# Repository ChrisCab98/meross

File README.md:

# meross
Meross SmartSurge compatible with HomeKit

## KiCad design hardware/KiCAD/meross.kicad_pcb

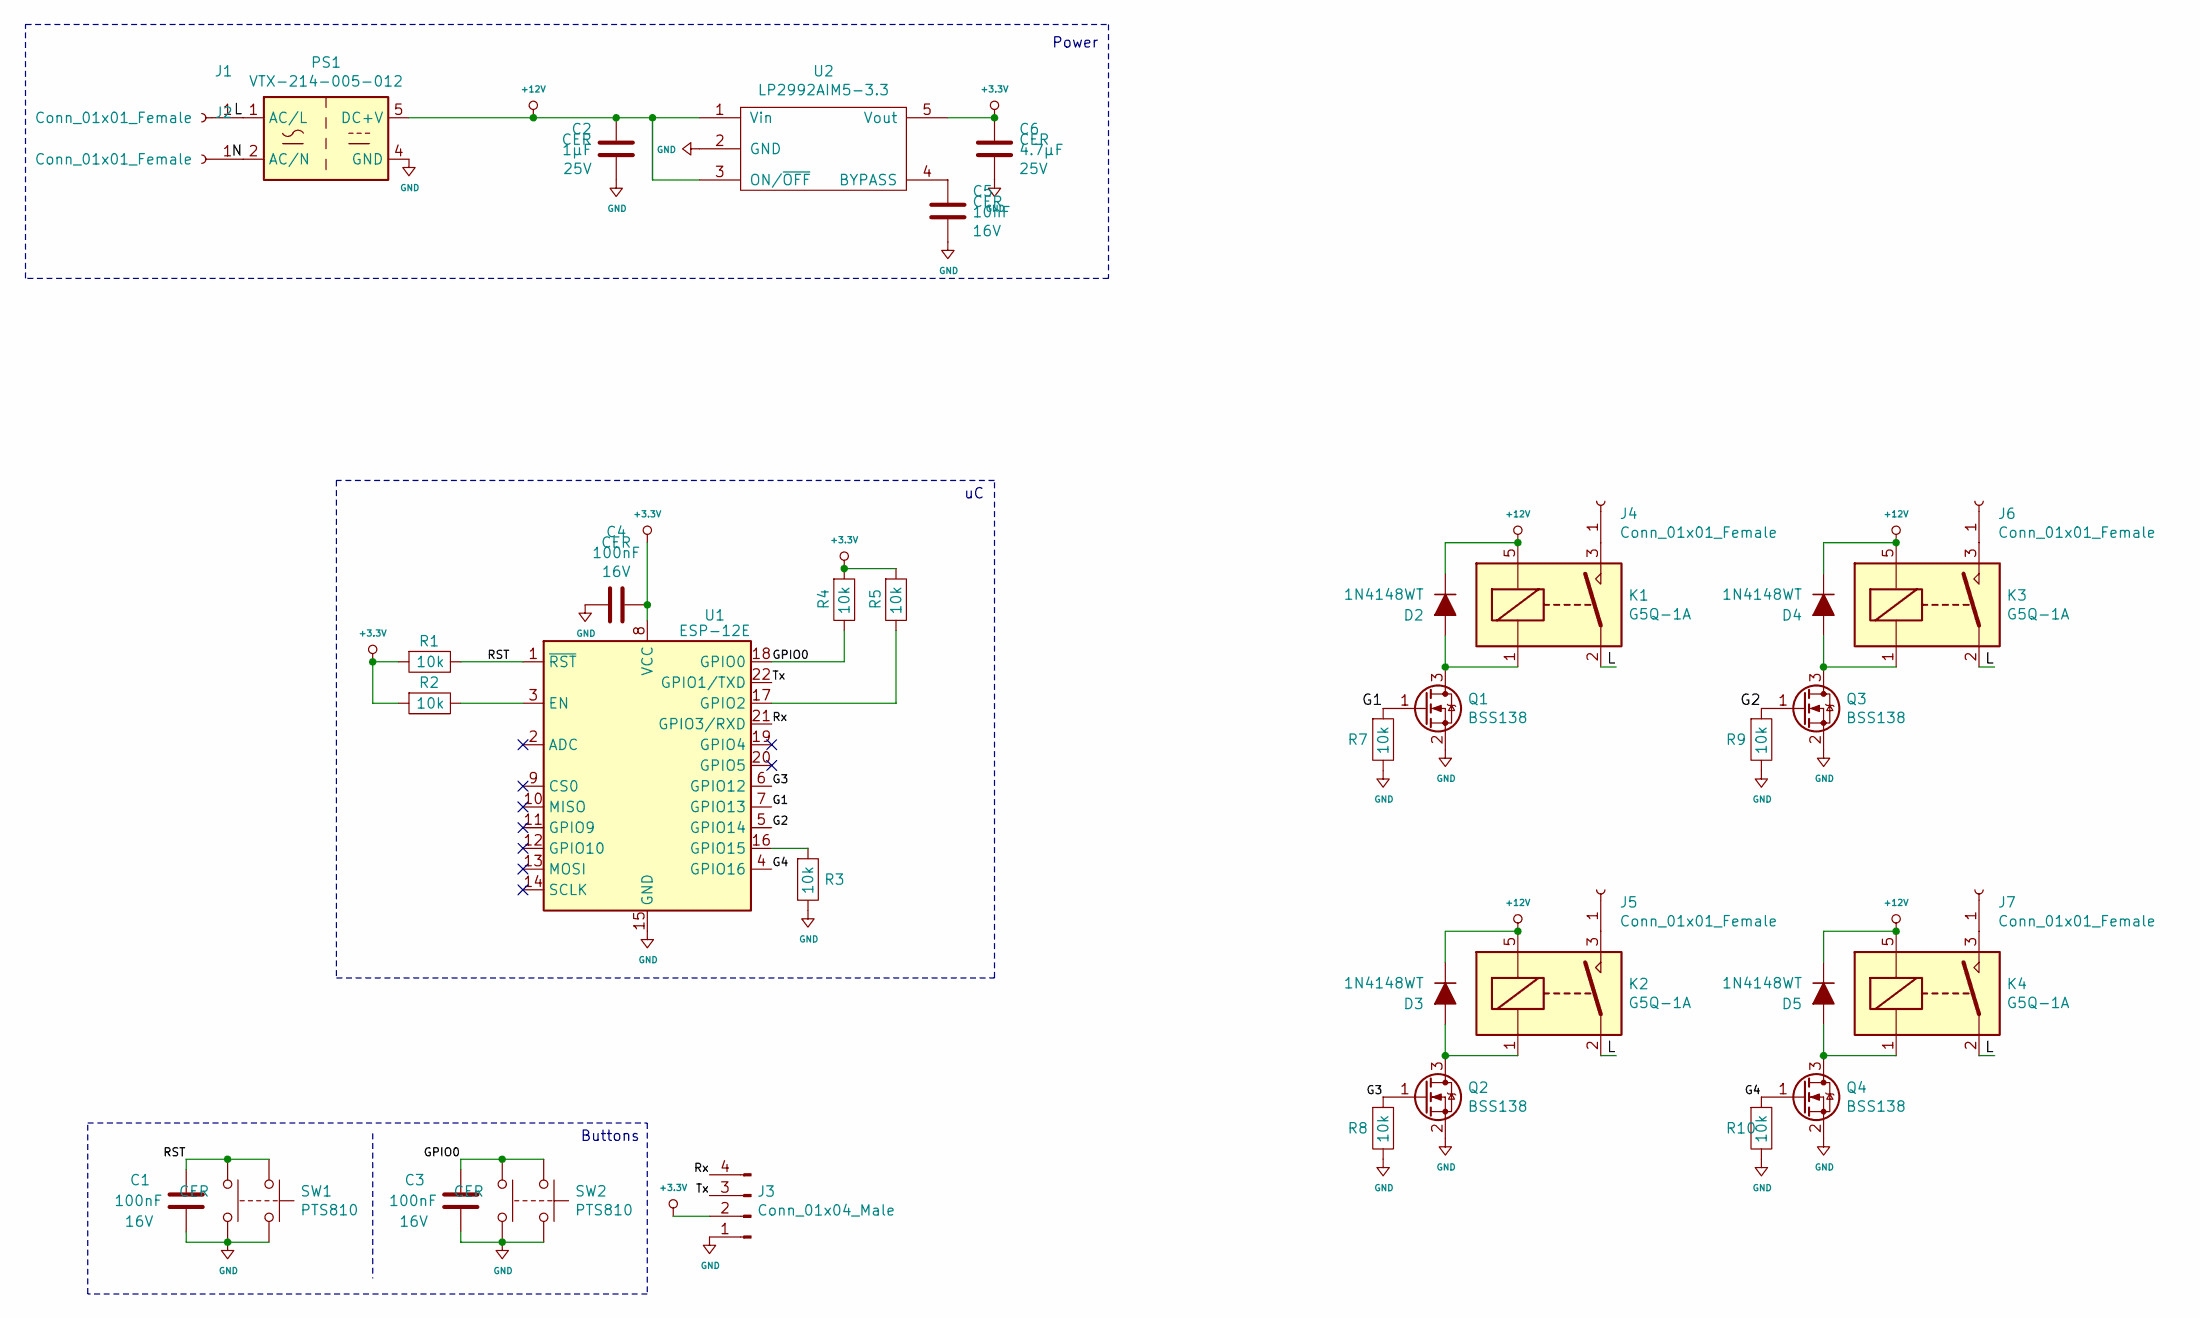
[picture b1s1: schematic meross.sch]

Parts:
C1, C3, C4: C_0029; C_0603
C2: C_0037; C_0603
C5: C_0017; C_0603
C6: C_0036; C_0603
D2, D3, D4, D5: D_0022; D_SOD-523
J1, J2, J4, J5, J6, J7: Conn_01x01_Female; TestPoint_Loop_D2.54mm_Drill1.5mm_Beaded
J3: Conn_01x04_Male; PinHeader_2x02_P2.54mm_Vertical
K1, K2, K3, K4: G5Q-1A; Relay_SPST_Omron-G5Q-1A
PS1: VTX-214-005-012
Q1, Q2, Q3, Q4: BSS138; SOT-23
R1, R2, R3, R4, R5, R7, R8, R9, R10: R_0065; R_0603
SW1, SW2: SW_0003; PTS810
U1: ESP-12E
U2: U_0005; SOT_23-5

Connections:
+3.3V: C4.1, C6.1, J3.2, R1.1, R2.1, R4.1, R5.1, U1.8 (VCC), U2.5 (Vout)
+12V: C2.2, D2.1 (K), D3.1 (K), D4.1 (K), D5.1 (K), K1.5, K2.5, K3.5, K4.5, PS1.5 (DC+V), U2.1 (Vin), U2.3 (ON/~OFF)
/G1: Q1.1 (G), R7.1, U1.7 (GPIO13)
/G2: Q3.1 (G), R9.1, U1.5 (GPIO14)
/G3: Q2.1 (G), R8.1, U1.6 (GPIO12)
/G4: Q4.1 (G), R10.1, U1.4 (GPIO16)
/GPIO0: C3.2, R4.2, SW2.1, SW2.2, U1.18 (GPIO0)
/L: J1.1, K1.2, K2.2, K3.2, K4.2, PS1.1 (AC/L)
/N: J2.1, PS1.2 (AC/N)
/RST: C1.2, R1.2, SW1.1, SW1.2, U1.1 (~RST)
/Rx: J3.4, U1.21 (GPIO3/RXD)
/Tx: J3.3, U1.22 (GPIO1/TXD)
GND: C1.1, C2.1, C3.1, C4.2, C5.2, C6.2, J3.1, PS1.4 (GND), Q1.2 (S), Q2.2 (S), Q3.2 (S), Q4.2 (S), R3.2, R7.2, R8.2, R9.2, R10.2, SW1.3, SW1.4, SW2.3, SW2.4, U1.15 (GND), U2.2 (GND)
unnamed: C5.1, U2.4 (BYPASS)
unnamed: D2.2 (A), K1.1, Q1.3 (D)
unnamed: D3.2 (A), K2.1, Q2.3 (D)
unnamed: D4.2 (A), K3.1, Q3.3 (D)
unnamed: D5.2 (A), K4.1, Q4.3 (D)
unnamed: J4.1, K1.3
unnamed: J5.1, K2.3
unnamed: J6.1, K3.3
unnamed: J7.1, K4.3
unnamed: R2.2, U1.3 (EN)
unnamed: R3.1, U1.16 (GPIO15)
unnamed: R5.2, U1.17 (GPIO2)

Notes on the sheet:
Buttons
Power

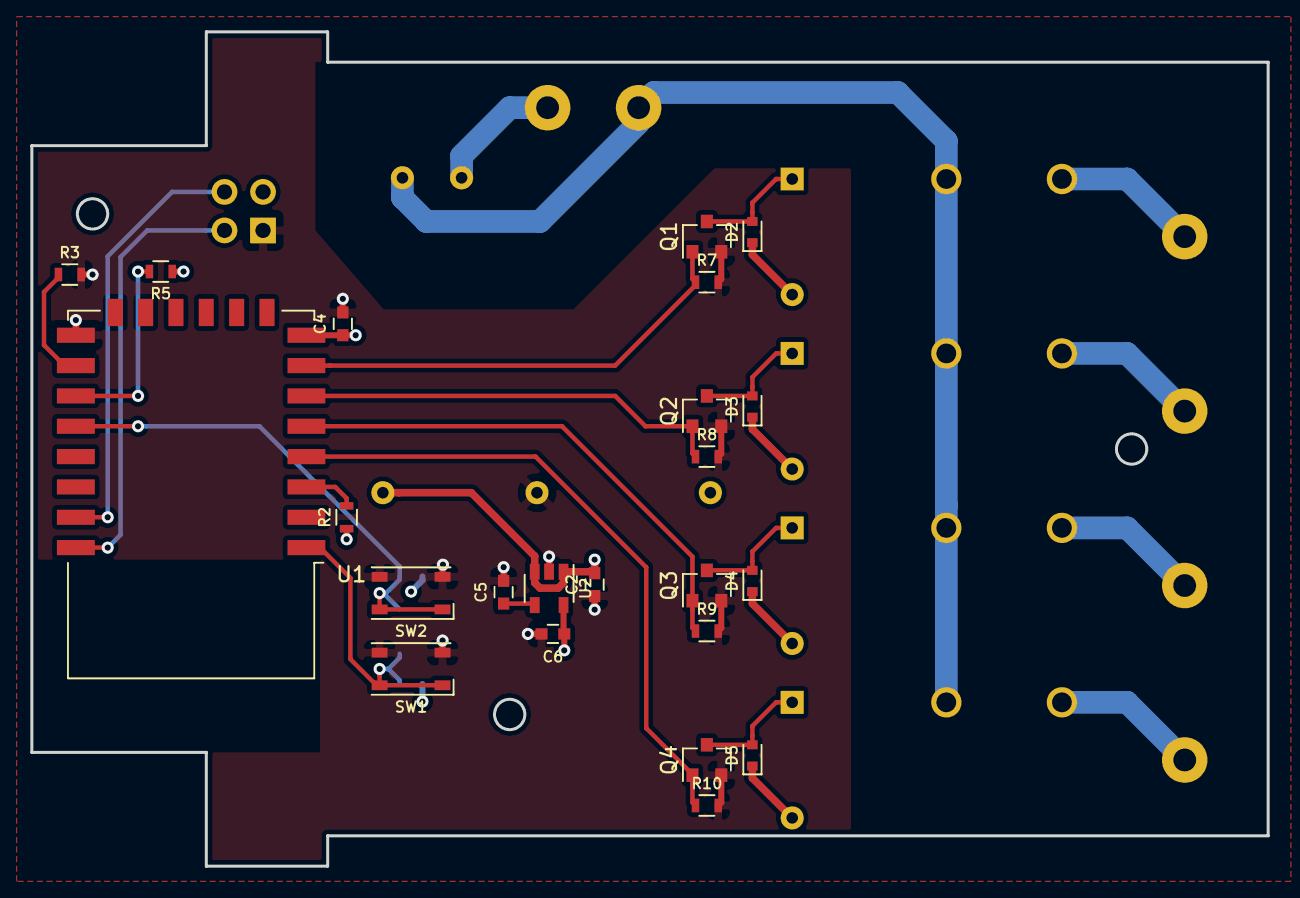
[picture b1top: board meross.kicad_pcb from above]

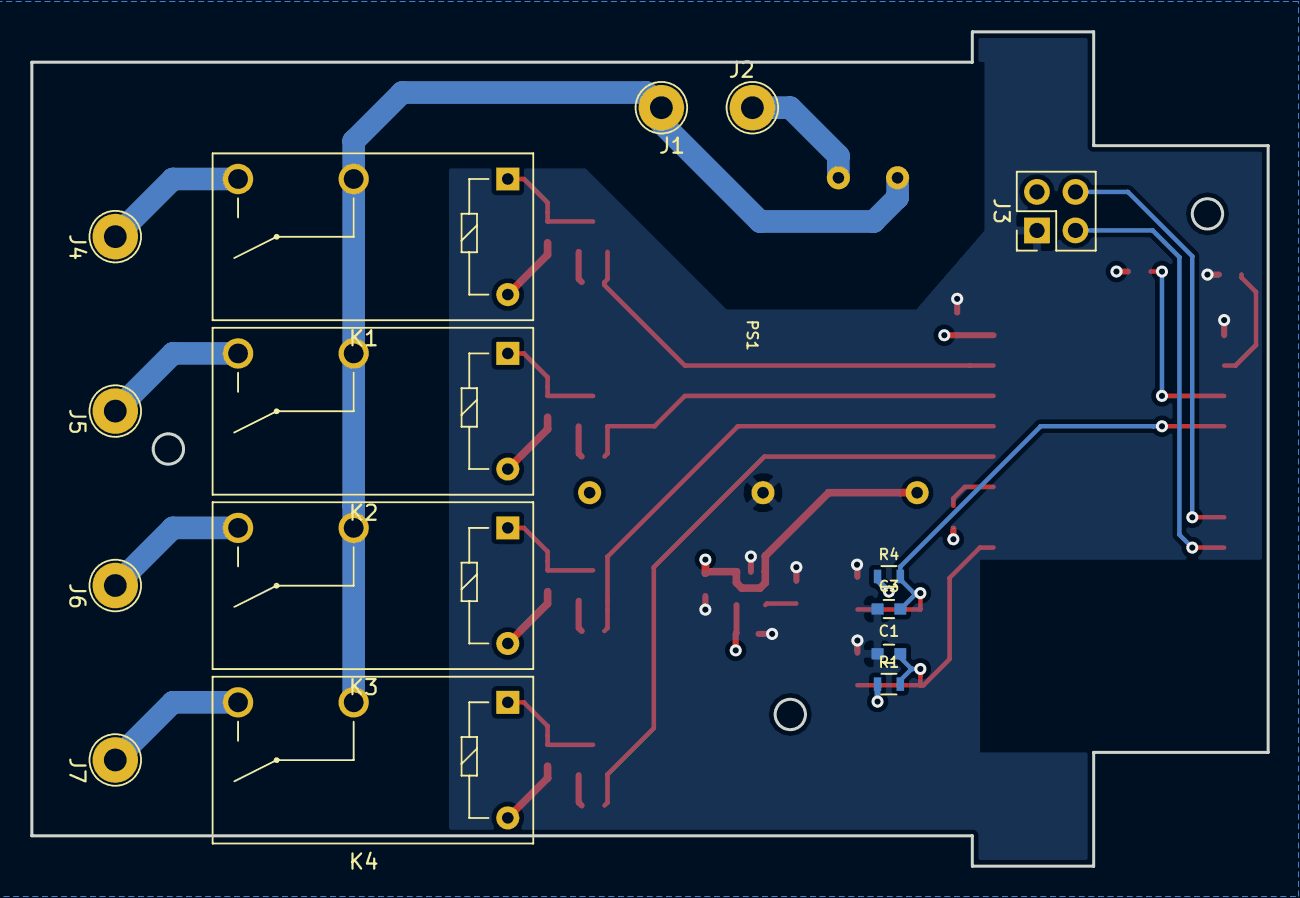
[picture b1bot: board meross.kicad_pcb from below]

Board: 4 copper layers, 81.5 x 55.0 mm, 39 parts (16 on the bottom side), 25 nets.

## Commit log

2019-08-24 add software folder
2019-08-24 add hardware folder
2019-08-24 add 3d models
2019-08-24 cd .ino file
2019-12-29 v1.0.0
